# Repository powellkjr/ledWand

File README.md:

# ledWand
a attiny based argb wand

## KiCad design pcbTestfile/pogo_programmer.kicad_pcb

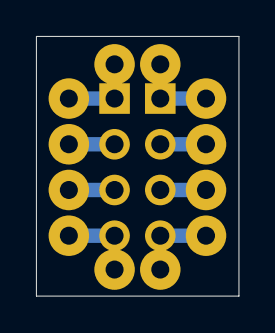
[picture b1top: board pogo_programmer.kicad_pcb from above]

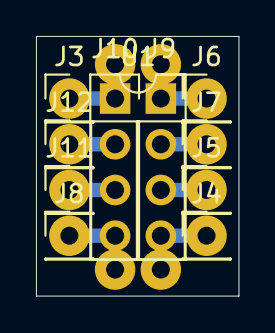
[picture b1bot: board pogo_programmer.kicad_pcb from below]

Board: 2 copper layers, 11.2 x 14.4 mm, 11 parts (11 on the bottom side), 8 nets.

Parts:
J3, J4, J5, J6, J7, J8, J11, J12: Conn_01x01_Pin; PogoPin_1x01_P2.54mm_1.0mmIDx2.0mmOD
J9, J10: Conn_01x04_Socket; PinSocket_1x04_P2.54mm_Vertical
U1: ATtiny85-20P; DIP-8_W7.62mm

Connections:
unnamed: J4.1, J9.4, U1.5 (AREF/PB0)
unnamed: J5.1, J9.3, U1.6 (PB1)
unnamed: J6.1, J9.1, U1.8 (VCC)
unnamed: J7.1, J9.2, U1.7 (PB2)
unnamed: J3.1, J10.1, U1.1 (~RESET/PB5)
unnamed: J10.2, J12.1, U1.2 (XTAL1/PB3)
unnamed: J10.3, J11.1, U1.3 (XTAL2/PB4)
unnamed: J8.1, J10.4, U1.4 (GND)

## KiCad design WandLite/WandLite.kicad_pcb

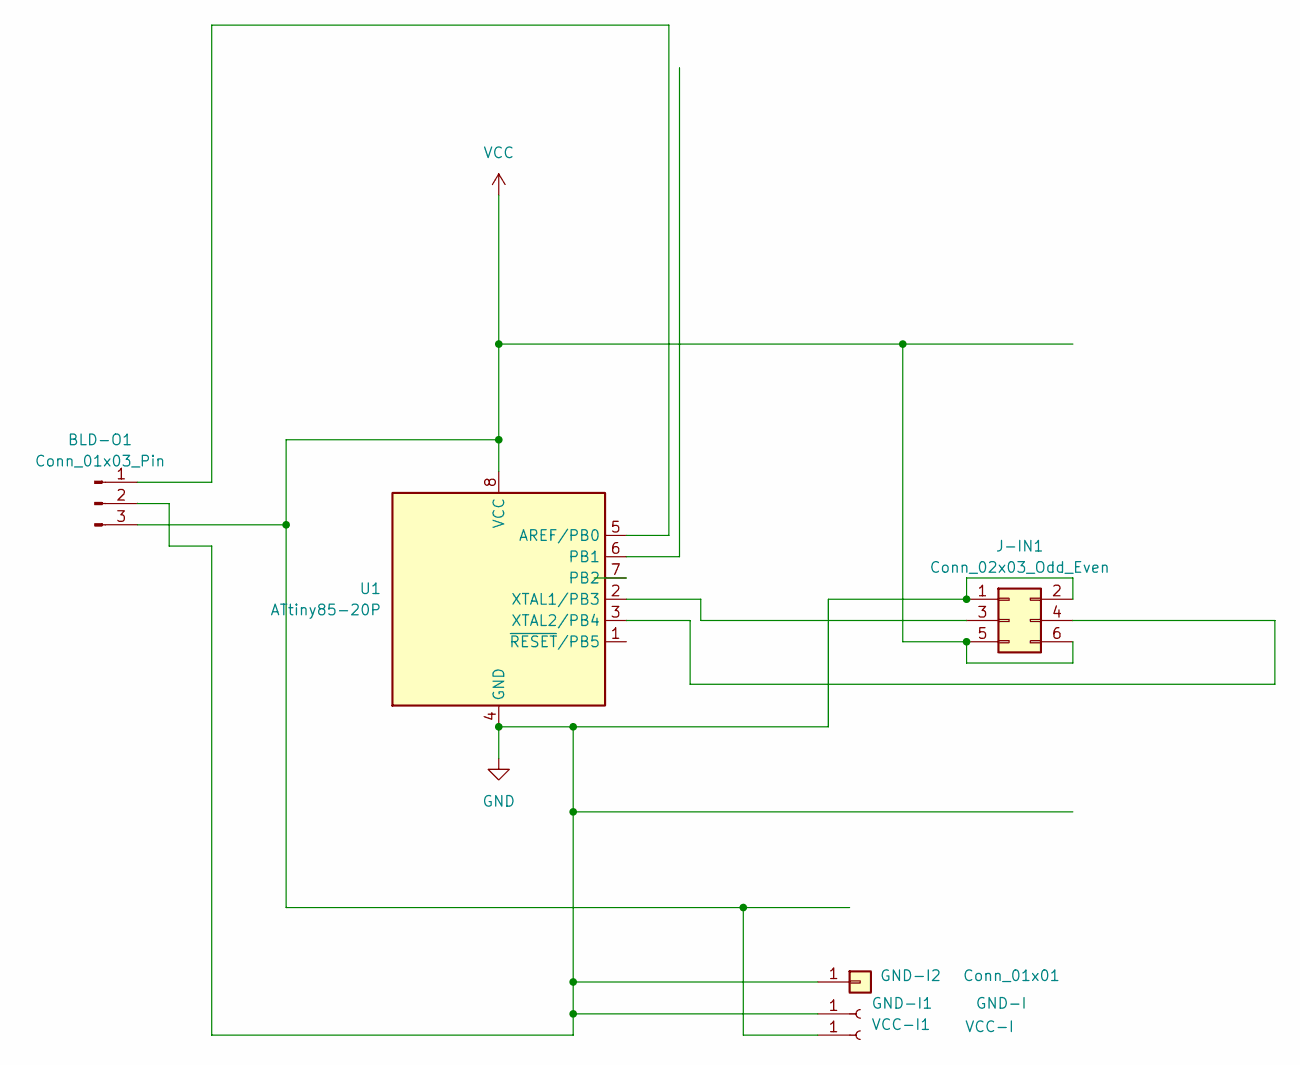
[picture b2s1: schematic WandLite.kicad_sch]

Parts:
BLD-O1: Conn_01x03_Pin; JST_PH_S3B-PH-K_1x03_P2.00mm_Horizontal
GND-I1: GND-I; SolderWire-0.15sqmm_1x01_D0.5mm_OD1.5mm
GND-I2: Conn_01x01; SolderWire-0.15sqmm_1x01_D0.5mm_OD1.5mm
J-IN1: Conn_02x03_Odd_Even; PinHeader_2x03_P2.54mm_Vertical
U1: ATtiny85-20P; DIP-8_W7.62mm
VCC-I1: VCC-I; SolderWire-0.15sqmm_1x01_D0.5mm_OD1.5mm

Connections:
GND: BLD-O1.2, GND-I1.1, GND-I2.1, J-IN1.1, J-IN1.2, U1.4 (GND)
unnamed: BLD-O1.1, U1.5 (AREF/PB0)
unnamed: J-IN1.3, U1.2 (XTAL1/PB3)
unnamed: J-IN1.4, U1.3 (XTAL2/PB4)
VCC: BLD-O1.3, J-IN1.5, J-IN1.6, U1.8 (VCC), VCC-I1.1

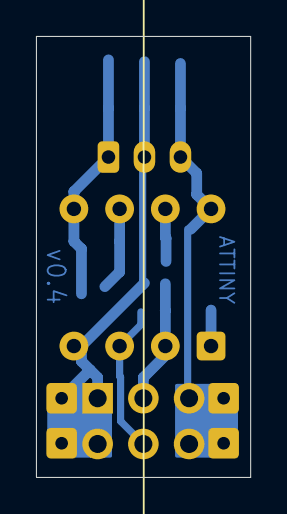
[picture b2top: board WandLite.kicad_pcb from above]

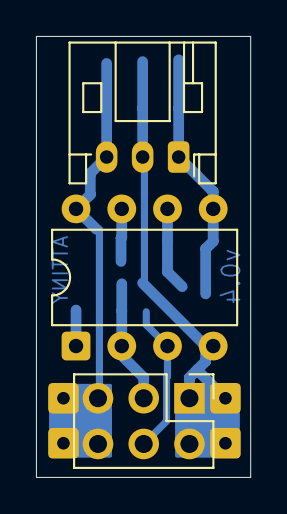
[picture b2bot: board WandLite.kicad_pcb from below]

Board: 2 copper layers, 11.9 x 24.5 mm, 6 parts (6 on the bottom side), 5 nets.

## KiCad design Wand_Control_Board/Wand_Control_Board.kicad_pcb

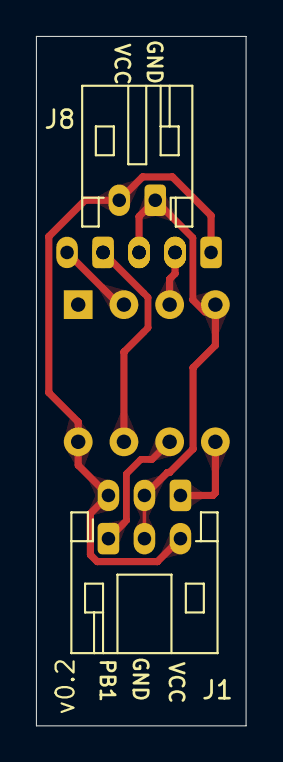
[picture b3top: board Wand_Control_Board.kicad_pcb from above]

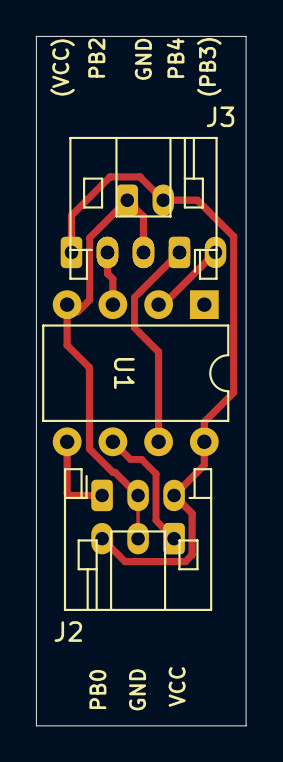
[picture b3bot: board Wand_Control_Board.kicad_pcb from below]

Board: 2 copper layers, 11.6 x 38.3 mm, 6 parts (4 on the bottom side), 7 nets.

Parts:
J1, J2, J3: Conn_01x03_Socket; JST_PH_S3B-PH-K_1x03_P2.00mm_Horizontal
J5: Conn_01x05_Socket; JST_PH_B5B-PH-K_1x05_P2.00mm_Vertical
J8: Conn_01x02_Socket; JST_PH_S2B-PH-K_1x02_P2.00mm_Horizontal
U1: ATtiny85-20P; DIP-8_W7.62mm

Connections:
GND: J1.2, J2.2, J3.2, J5.3, J8.1, U1.4 (GND)
unnamed: J1.1, U1.6 (PB1)
unnamed: J2.1, U1.5 (AREF/PB0)
unnamed: J3.1, J5.4, U1.7 (PB2)
unnamed: J3.3, J5.2, U1.3 (XTAL2/PB4)
unnamed: J5.5, U1.2 (XTAL1/PB3)
VCC: J1.3, J2.3, J5.1, J8.2, U1.8 (VCC)

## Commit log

2025-04-28 control board pcb and program
2025-04-28 added unneeded prog pad
2025-04-28 removed unneeded progam pad
2025-04-30 outputs and cleaner silkscreen
2025-04-30 flipped parts to make solder easier
2025-04-30 plots
2025-05-01 wrong models saved
2025-05-01 added pdf
2025-05-12 added lite board
2025-05-12 inside routed to save some width
2025-05-12 short relief and output
2025-05-14 removed mode- for vcc-c
2025-05-24 flipped board to BU
2025-05-28 adding programer
2025-06-13 v5 made vertical
2025-06-28 inverted for soldering
